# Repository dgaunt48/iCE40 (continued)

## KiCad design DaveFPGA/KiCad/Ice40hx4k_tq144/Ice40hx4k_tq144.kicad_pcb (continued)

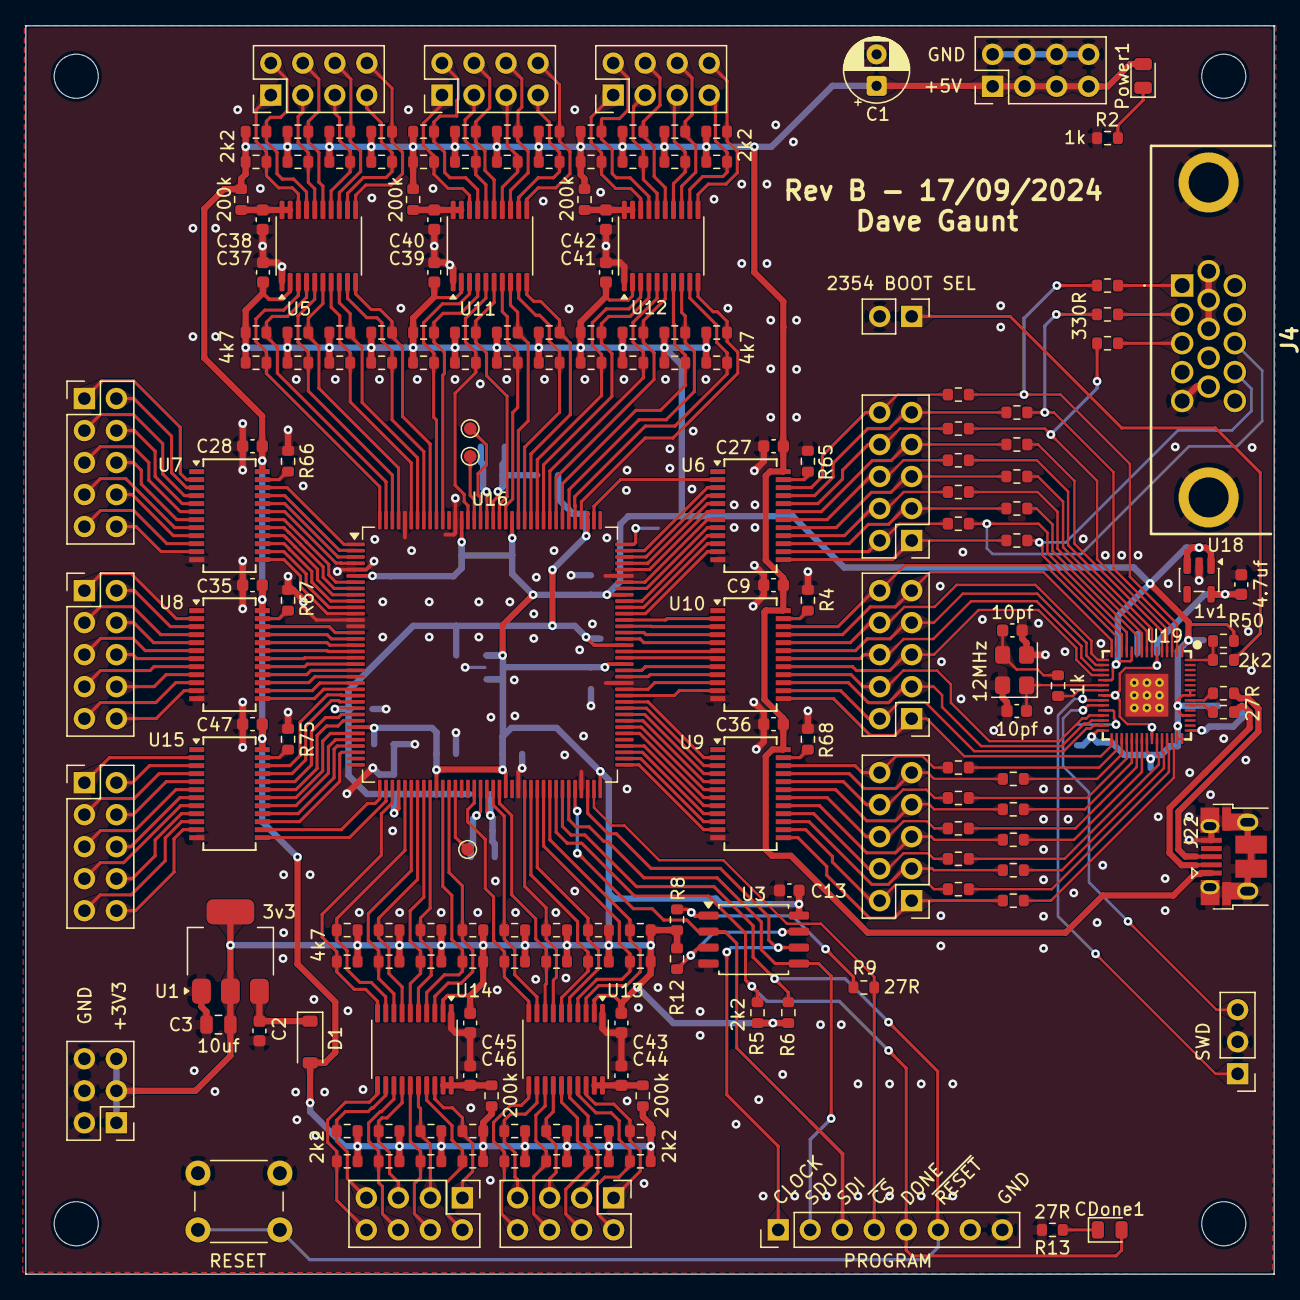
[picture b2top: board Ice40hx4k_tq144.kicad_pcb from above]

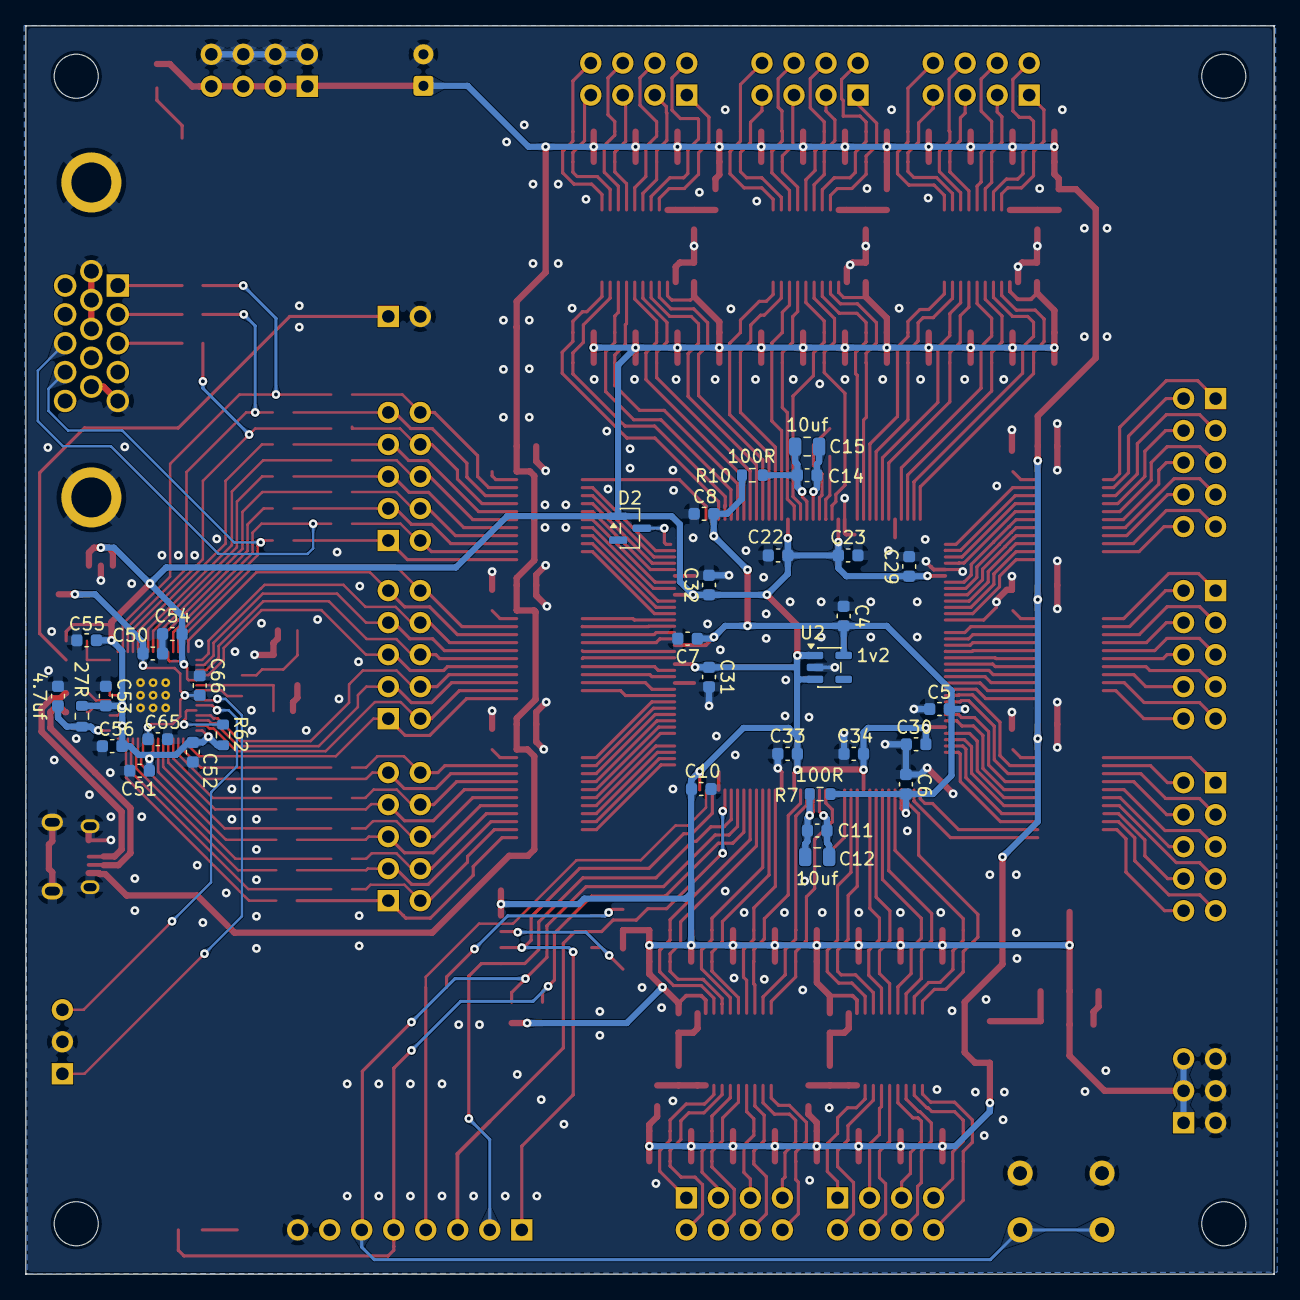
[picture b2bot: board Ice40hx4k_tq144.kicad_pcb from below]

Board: 2 copper layers, 99.1 x 99.1 mm, 229 parts (34 on the bottom side), 271 nets.

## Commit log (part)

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2026-05-02 - Added iCE40 LEDS, The FPGA version of Hello World!
2026-05-02 - Initial test of using the Vic20 display register values and memory dumps to draw a VGA screen.
2026-05-02 - Added VIA 6522 initial files.
2026-05-03 - Added basic Timer 1 functionality.
2026-05-03 - Added IRQ Pin And Timer 1 Interrupt.
2026-05-04 - VIA 6522 Timer 1 Passed Simulation.
2026-05-14 - Added Custom FPGA Board Files So I Can Use APIO Upload.
2026-05-14 - Batch File That Creates iCE40_BitSteam.h To Include Directly Into A .c Program.
2026-05-14 - Added iCE40_BitStream.h to gitignore as it is a generated file.
2026-05-14 - Added Missing Read IER Register.
2026-06-06 - Changed To A Faster Clock So I Can Update At The Correct Clock Edges.
2026-06-06 - Fixed A Bug With The IRQ Pin Introduced In The Previous Update.
2026-06-14 - Cursor is flashing on a real Vic20.
2026-06-14 - Add Output Port A No Handshake Register. - Clean Up New Timer Code.
2026-06-15 - Improved control of when the FPGA drives the data bus.
2026-06-20 - Vic20 KeyScan Is Rock Solid For The First Time With The 6522 FPGA.
2026-06-26 - Vic20 Keyboard Scan Finally Works.
